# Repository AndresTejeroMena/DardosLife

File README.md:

# DardosLife
DardosLife is a personal project for recreational and learning purposes in which I have transformed a basic commercial electronic dartboard into one that, 
through an Arduino, is capable of sending information about where a dart has impacted to the computer. Using GODOT on the computer, I have programmed seven different games: 
501 series, cricket, battleship, connect4, burma road, ludo and football. 

Its use for commercial purposes is not permitted. 
The game concepts of battleship and connect4 are original creations, and the creator does not allow their commercial exploitation without consent. <br>

<p align="center">
  Project developer: Andrés Tejero Mena (<a href="mailto:tejeromenaandres@gmail.com">tejeromenaandres@gmail.com</a>).
</p>

## How does it work?
https://youtu.be/JF_7bkpHpz4

To carry out this project, the first step was to understand how an electronic dartboard works on the inside. If you dismantle one, you'll see that the sensors consist of two sheets with circuits drawn on them, separated by an insulator. One sheet has 10 circuits and the other has 7, so when a dart hits the dartboard, one circuit makes contact with another, and we can determine where it has impacted.

Knowing this, I unsoldered the connectors of these sheets from the electronic board and used an Arduino to collect that information and output it through the serial port to the computer.
To do this, I designed a PCB with EAGLE and had it manufactured.

The Arduino program performs a loop of signal scanning through the 7-pin sheet and waits for the arrival of current through the 10-pin sheet. When one of those 10 pins detects the HIGH signal, it checks from which pin the signal was sent and to which pin it was received. Based on a predefined matrix, we know where the dart has impacted. All that's left is to send it via serial. Depending on the dartboard model, this matrix will vary, so I've created two different Arduino programs for two different dartboards.

At this point, we already have a dartboard capable of sending information to the computer. To program the games, I used GODOT, a very intuitive and easy-to-learn tool. In less than a month, I went from not knowing about GODOT's existence to having programmed 7 games. The only thing needed for it to work is to use a C# script to read the serial port and send that information to GODOT, where I programmed all the games in its GDScript language.

This has been a very enjoyable project that I wanted to share with you. The goal was always to challenge myself and learn; there were never any commercial purposes involved.
## What I've used:
Decathlon Canaveral ED110 electronic dartboard

Arduino Nano 33 Ble

Soldering iron

10 resistors of 10KOhm

Laptop

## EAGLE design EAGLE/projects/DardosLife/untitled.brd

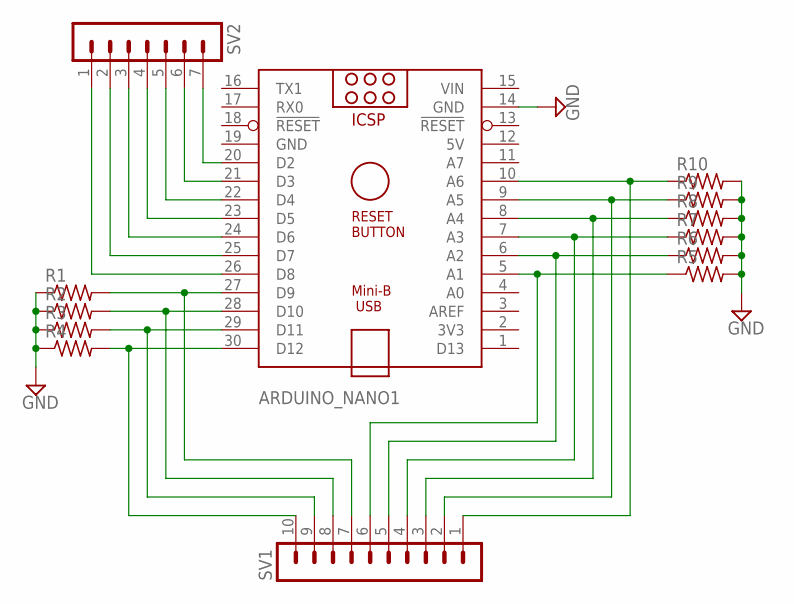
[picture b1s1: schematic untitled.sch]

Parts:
ARDUINO_NANO1: ARDUINO_NANO
R1, R2, R3, R4, R5, R6, R7, R8, R9, R10: R-US_0309/12; 0309/12
SV1: MA10-1
SV2: MA07-1

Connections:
5V: ARDUINO_NANO1.12 (5V)
GND: ARDUINO_NANO1.14 (GND), ARDUINO_NANO1.19 (GND), R1.1, R2.1, R3.1, R4.1, R5.2, R6.2, R7.2, R8.2, R9.2, R10.2
unnamed: ARDUINO_NANO1.30 (D12), R4.2, SV1.10
unnamed: ARDUINO_NANO1.29 (D11), R3.2, SV1.9
unnamed: ARDUINO_NANO1.28 (D10), R2.2, SV1.8
unnamed: ARDUINO_NANO1.27 (D9), R1.2, SV1.7
unnamed: ARDUINO_NANO1.5 (A1), R5.1, SV1.6
unnamed: ARDUINO_NANO1.6 (A2), R6.1, SV1.5
unnamed: ARDUINO_NANO1.7 (A3), R7.1, SV1.4
unnamed: ARDUINO_NANO1.8 (A4), R8.1, SV1.3
unnamed: ARDUINO_NANO1.9 (A5), R9.1, SV1.2
unnamed: ARDUINO_NANO1.10 (A6), R10.1, SV1.1
unnamed: ARDUINO_NANO1.26 (D8), SV2.1
unnamed: ARDUINO_NANO1.25 (D7), SV2.2
unnamed: ARDUINO_NANO1.24 (D6), SV2.3
unnamed: ARDUINO_NANO1.23 (D5), SV2.4
unnamed: ARDUINO_NANO1.22 (D4), SV2.5
unnamed: ARDUINO_NANO1.21 (D3), SV2.6
unnamed: ARDUINO_NANO1.20 (D2), SV2.7
VIN: ARDUINO_NANO1.15 (VIN)

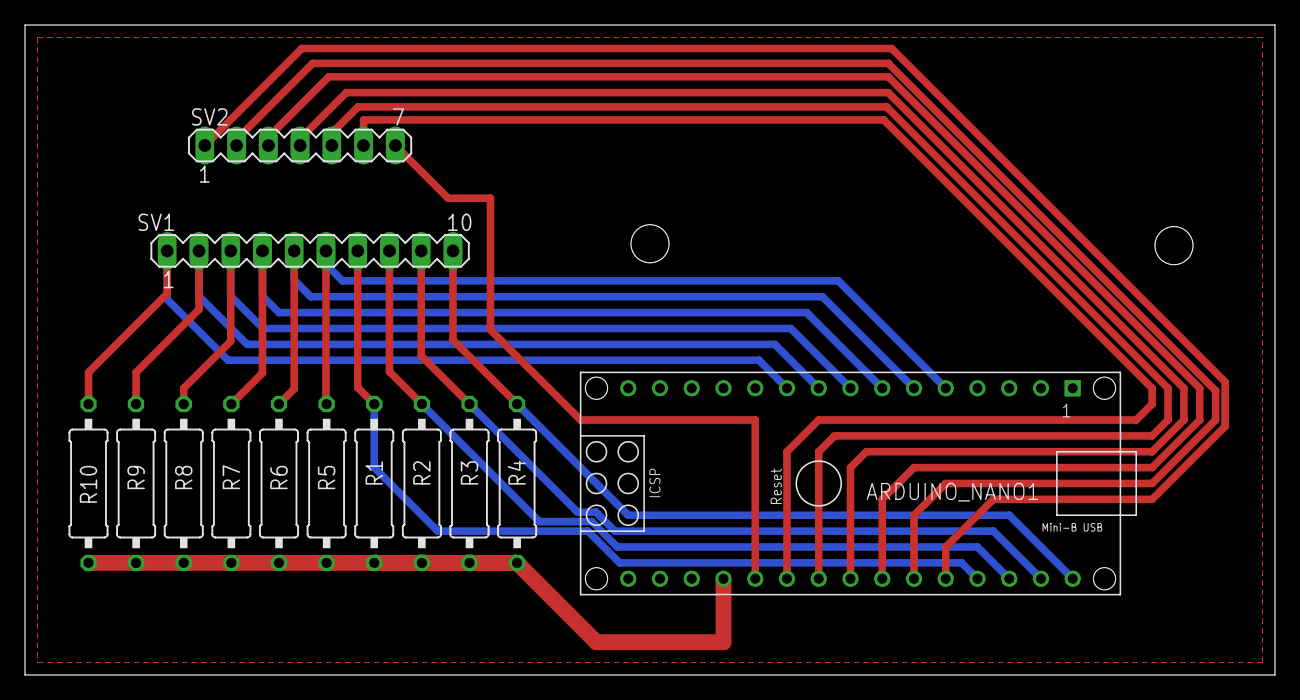
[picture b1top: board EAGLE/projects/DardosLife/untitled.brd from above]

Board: 2 copper layers, 100.0 x 52.0 mm, 13 parts (0 on the bottom side), 18 nets.

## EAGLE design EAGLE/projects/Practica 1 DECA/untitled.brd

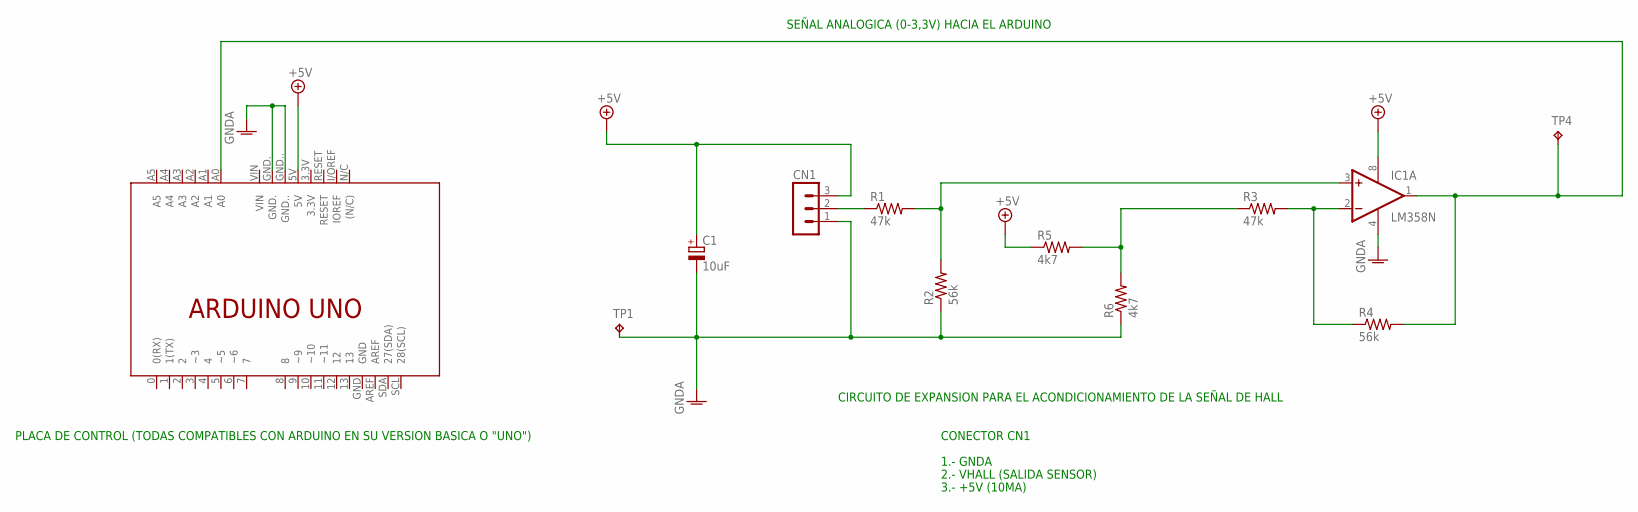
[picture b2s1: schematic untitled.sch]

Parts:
C1: 10uF; E5-10,5
CN1: MA03-1
IC1: LM358N; DIL08
R1, R3: 47k; R1206W
R2, R4: 56k; R1206W
R5, R6: 4k7; R1206W
TP1, TP4: TPPAD1-13Y; P1-13Y
U$1: ARDUINO_UNO_SPL; ARDUINO_UNO_REC

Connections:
+5V: C1.+, CN1.3, IC1.8 (V+), R5.1, U$1.5V
GNDA: C1.-, CN1.1, IC1.4 (V-), R2.1, R6.1, TP1.TP, U$1.GND., U$1.GND..
unnamed: CN1.2, R1.1
unnamed: R3.1, R5.2, R6.2
unnamed: IC1.3 (+IN), R1.2, R2.2
unnamed: IC1.2 (-IN), R3.2, R4.1
unnamed: IC1.1 (OUT), R4.2, TP4.TP, U$1.A0

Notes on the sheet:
PLACA DE CONTROL (TODAS COMPATIBLES CON ARDUINO EN SU VERSION BASICA O "UNO")
CIRCUITO DE EXPANSION PARA EL ACONDICIONAMIENTO DE LA SEÑAL DE HALL
CONECTOR CN1
1.- GNDA
2.- VHALL (SALIDA SENSOR)
3.- +5V (10MA)
SEÑAL ANALOGICA (0-3,3V) HACIA EL ARDUINO

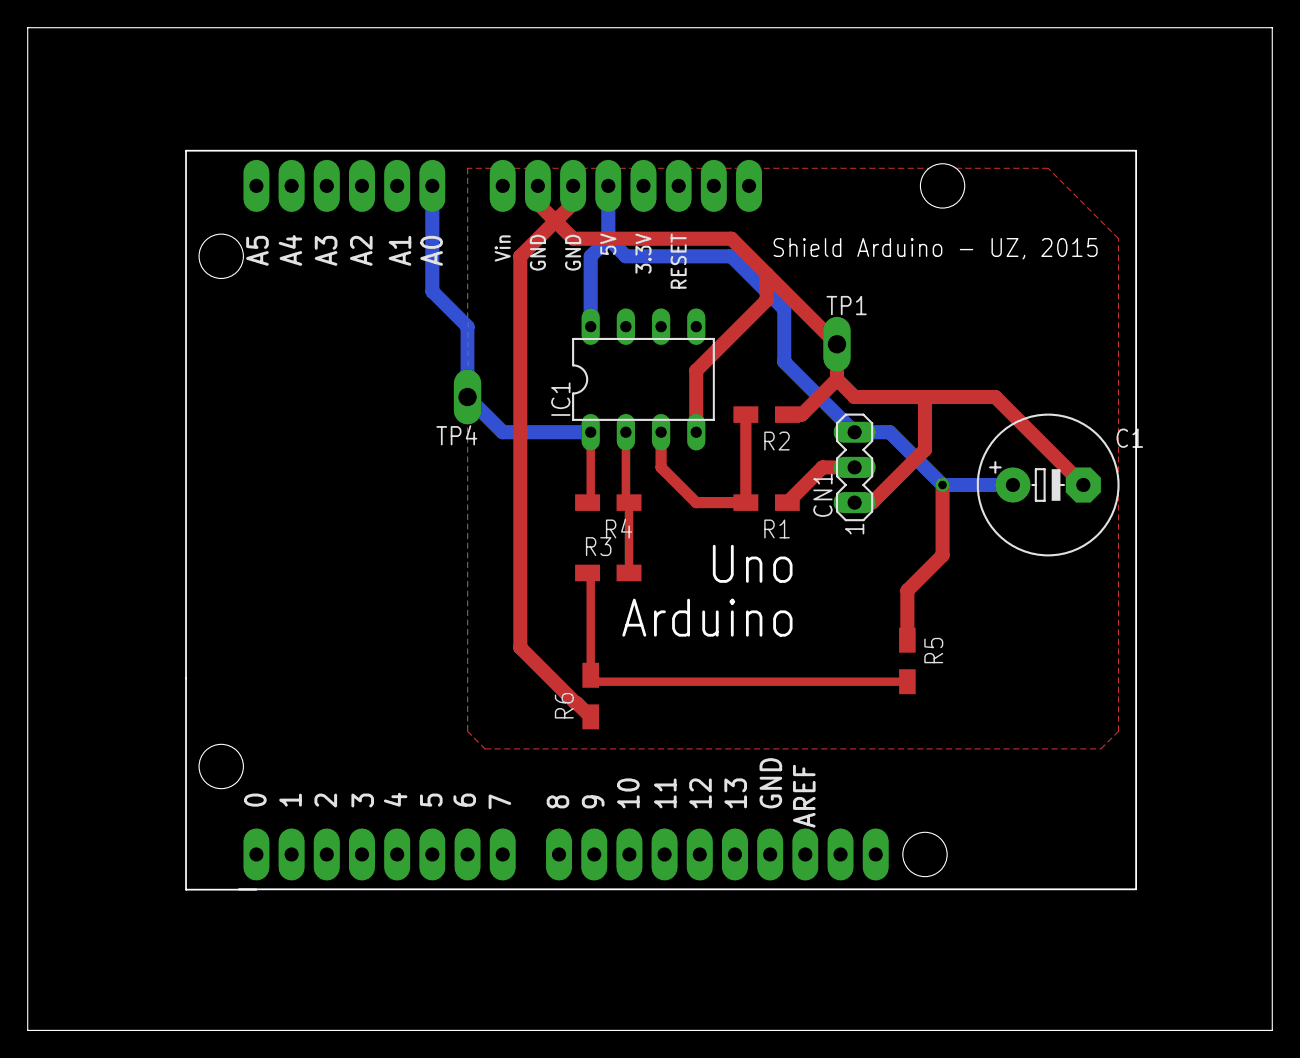
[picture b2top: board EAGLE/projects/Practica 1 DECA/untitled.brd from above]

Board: 2 copper layers, 89.7 x 72.3 mm, 12 parts (0 on the bottom side), 7 nets.

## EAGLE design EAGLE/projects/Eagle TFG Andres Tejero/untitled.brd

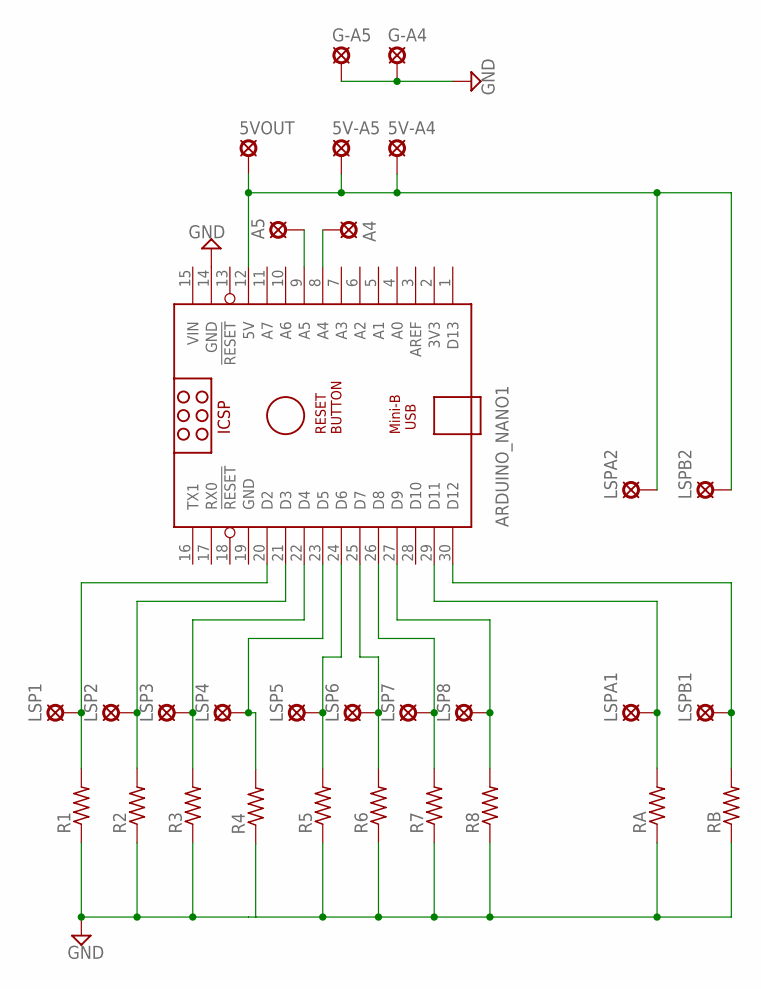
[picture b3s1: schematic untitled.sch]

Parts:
5V-A4, 5V-A5, 5VOUT: LSP10
A4, A5: LSP10
ARDUINO_NANO1: ARDUINO_NANO
G-A4, G-A5: LSP10
LSP1, LSP2, LSP3, LSP4, LSP5, LSP6, LSP7, LSP8: LSP10
LSPA1, LSPA2: LSP10
LSPB1, LSPB2: LSP10
R1, R2, R3, R4, R5, R6, R7, R8: R-US_0309/12; 0309/12
RA: R-US_0309/12; 0309/12
RB: R-US_0309/12; 0309/12

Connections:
GND: ARDUINO_NANO1.14 (GND), ARDUINO_NANO1.19 (GND), G-A4.MP, G-A5.MP, R1.1, R2.1, R3.1, R4.1, R5.1, R6.1, R7.1, R8.1, RA.1, RB.1
unnamed: 5V-A4.MP, 5V-A5.MP, 5VOUT.MP, ARDUINO_NANO1.12 (5V), LSPA2.MP, LSPB2.MP
unnamed: ARDUINO_NANO1.20 (D2), LSP1.MP, R1.2
unnamed: A5.MP, ARDUINO_NANO1.9 (A5)
unnamed: ARDUINO_NANO1.21 (D3), LSP2.MP, R2.2
unnamed: ARDUINO_NANO1.22 (D4), LSP3.MP, R3.2
unnamed: ARDUINO_NANO1.23 (D5), LSP4.MP, R4.2
unnamed: ARDUINO_NANO1.24 (D6), LSP5.MP, R5.2
unnamed: ARDUINO_NANO1.25 (D7), LSP6.MP, R6.2
unnamed: ARDUINO_NANO1.26 (D8), LSP7.MP, R7.2
unnamed: ARDUINO_NANO1.27 (D9), LSP8.MP, R8.2
unnamed: ARDUINO_NANO1.30 (D12), LSPB1.MP, RB.2
unnamed: ARDUINO_NANO1.29 (D11), LSPA1.MP, RA.2
unnamed: A4.MP, ARDUINO_NANO1.8 (A4)
VIN: ARDUINO_NANO1.15 (VIN)

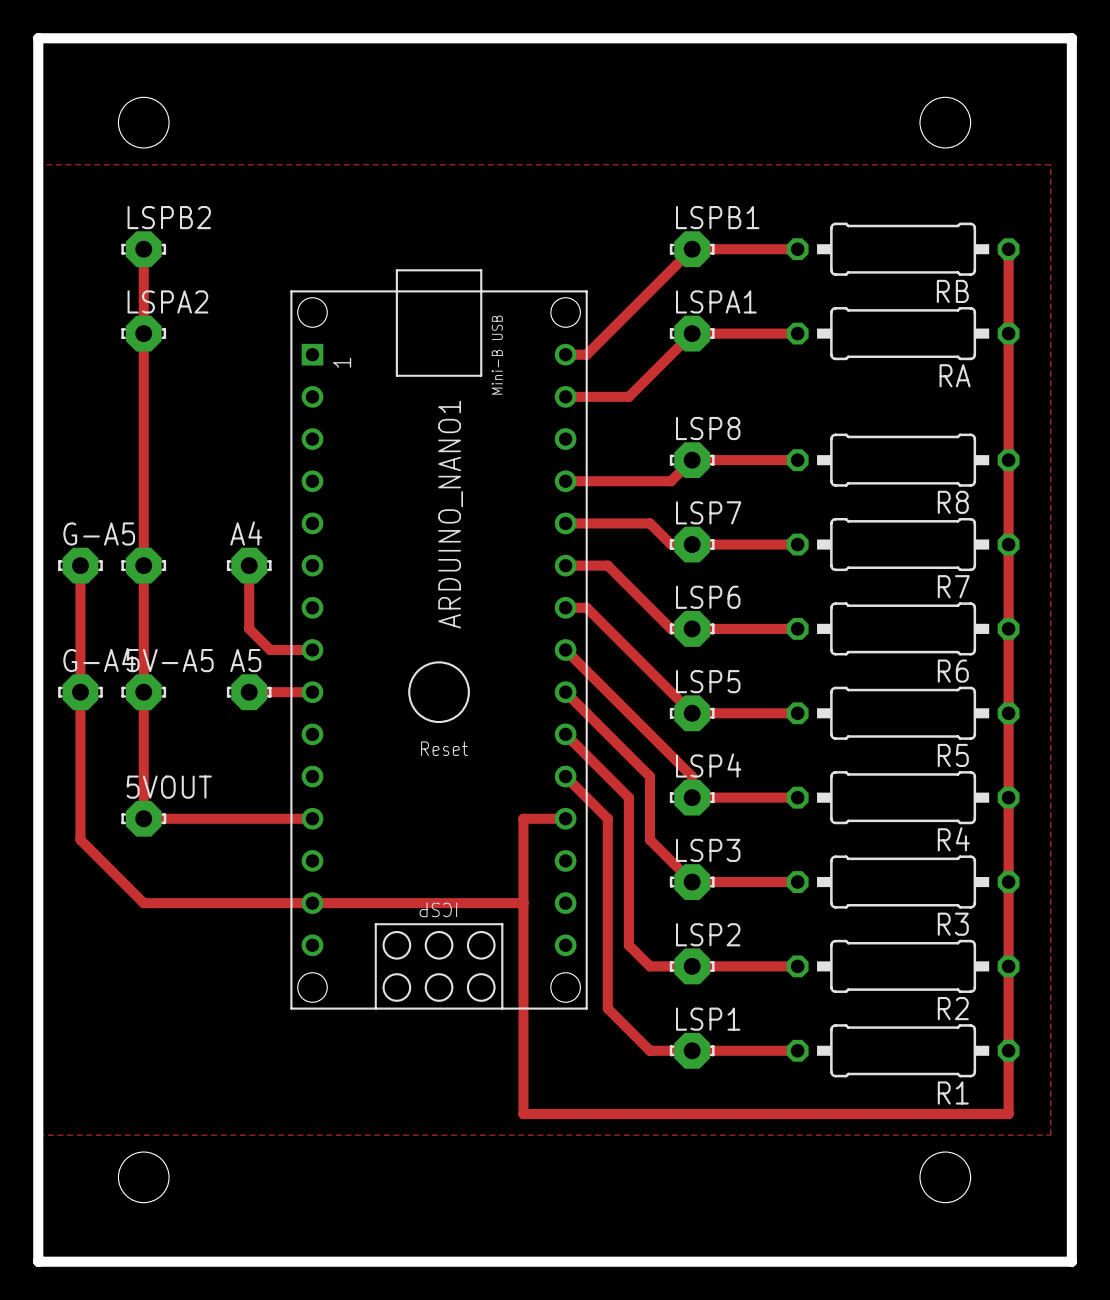
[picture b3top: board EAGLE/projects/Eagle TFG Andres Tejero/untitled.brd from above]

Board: 2 copper layers, 62.2 x 73.7 mm, 30 parts (0 on the bottom side), 14 nets.

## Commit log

2024-02-17 Subir Proyecto
2024-02-26 Publico Arduinos
2024-02-26 Publico Eagle
2024-02-26 Publicar GODOT
2024-02-28 Ajuste TLDR para uso con ArduinoNano
2025-02-28 Actualiza la carpeta Escenas con nuevos contenidos
2025-02-28 Actualiza la carpeta Scripts con nuevas modificaciones
